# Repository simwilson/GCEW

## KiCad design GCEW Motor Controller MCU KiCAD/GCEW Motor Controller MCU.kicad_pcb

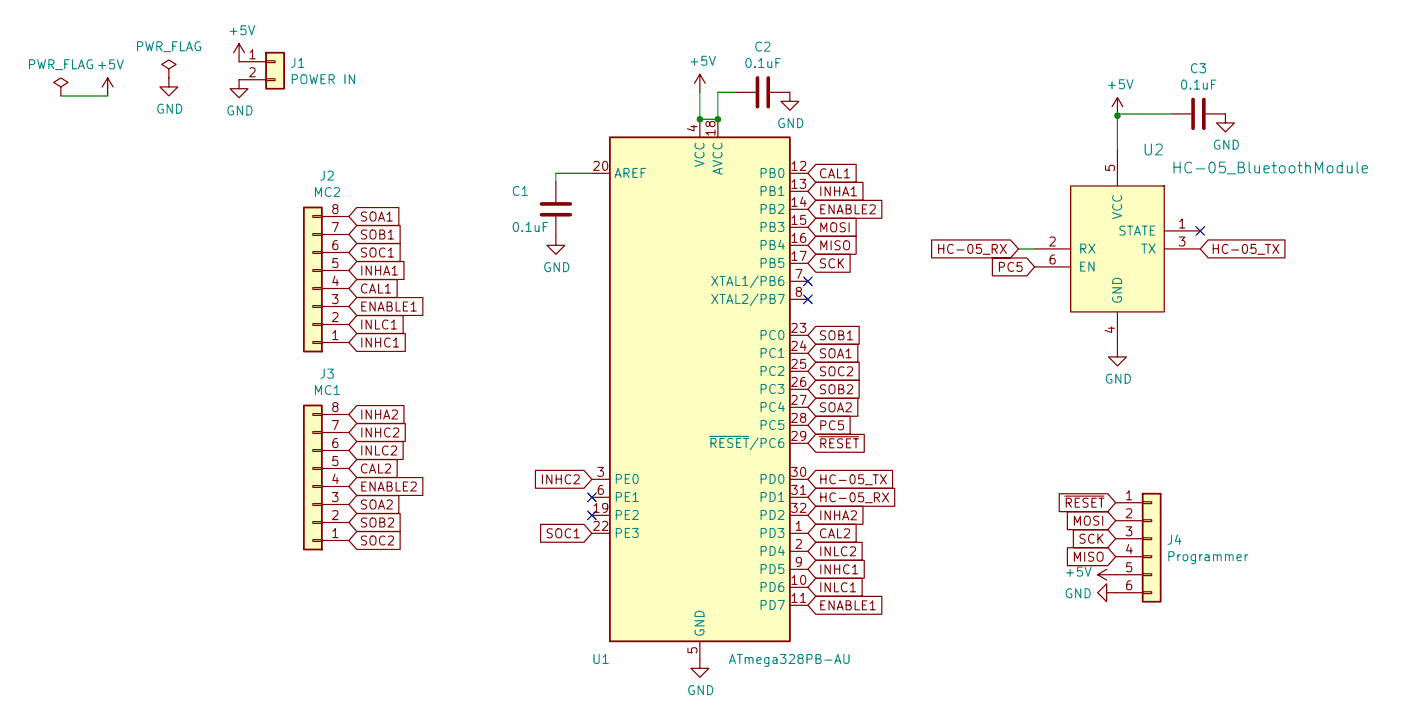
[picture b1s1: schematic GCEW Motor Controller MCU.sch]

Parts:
C1, C2, C3: 0.1uF; C_1206
J1: POWER IN; PhoenixContact_1984963_2-Pin-Connector_8A_P3.5mm
J2: MC2; PhoenixContact_1985027_8-Pin-Connector_8A_P3.5mm
J3: MC1; PhoenixContact_1985027_8-Pin-Connector_8A_P3.5mm
J4: Programmer; Pin_Header_Straight_2x03_Pitch2.54mm
U1: ATmega328PB-AU; TQFP-32_7x7mm_Pitch0.8mm
U2: HC-05_BluetoothModule; Pin_Header_Straight_1x06_Pitch2.54mm

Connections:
+5V: C2.2, C3.1, J1.1, J4.5, U1.4 (VCC), U1.18 (AVCC), U2.5 (VCC)
CAL1: J2.4, U1.12 (PB0)
CAL2: J3.5, U1.1 (PD3)
ENABLE1: J2.3, U1.11 (PD7)
ENABLE2: J3.4, U1.14 (PB2)
GND: C1.2, C2.1, C3.2, J1.2, J4.6, U1.5 (GND), U1.21 (GND), U2.4 (GND)
HC-05_RX: U1.31 (PD1), U2.2 (RX)
HC-05_TX: U1.30 (PD0), U2.3 (TX)
INHA1: J2.5, U1.13 (PB1)
INHA2: J3.8, U1.32 (PD2)
INHC1: J2.1, U1.9 (PD5)
INHC2: J3.7, U1.3 (PE0)
INLC1: J2.2, U1.10 (PD6)
INLC2: J3.6, U1.2 (PD4)
MISO: J4.4, U1.16 (PB4)
MOSI: J4.2, U1.15 (PB3)
unnamed: C1.1, U1.20 (AREF)
PC5: U1.28 (PC5), U2.6 (EN)
SCK: J4.3, U1.17 (PB5)
SOA1: J2.8, U1.24 (PC1)
SOA2: J3.3, U1.27 (PC4)
SOB1: J2.7, U1.23 (PC0)
SOB2: J3.2, U1.26 (PC3)
SOC1: J2.6, U1.22 (PE3)
SOC2: J3.1, U1.25 (PC2)
~RESET: J4.1, U1.29 (~RESET~/PC6)

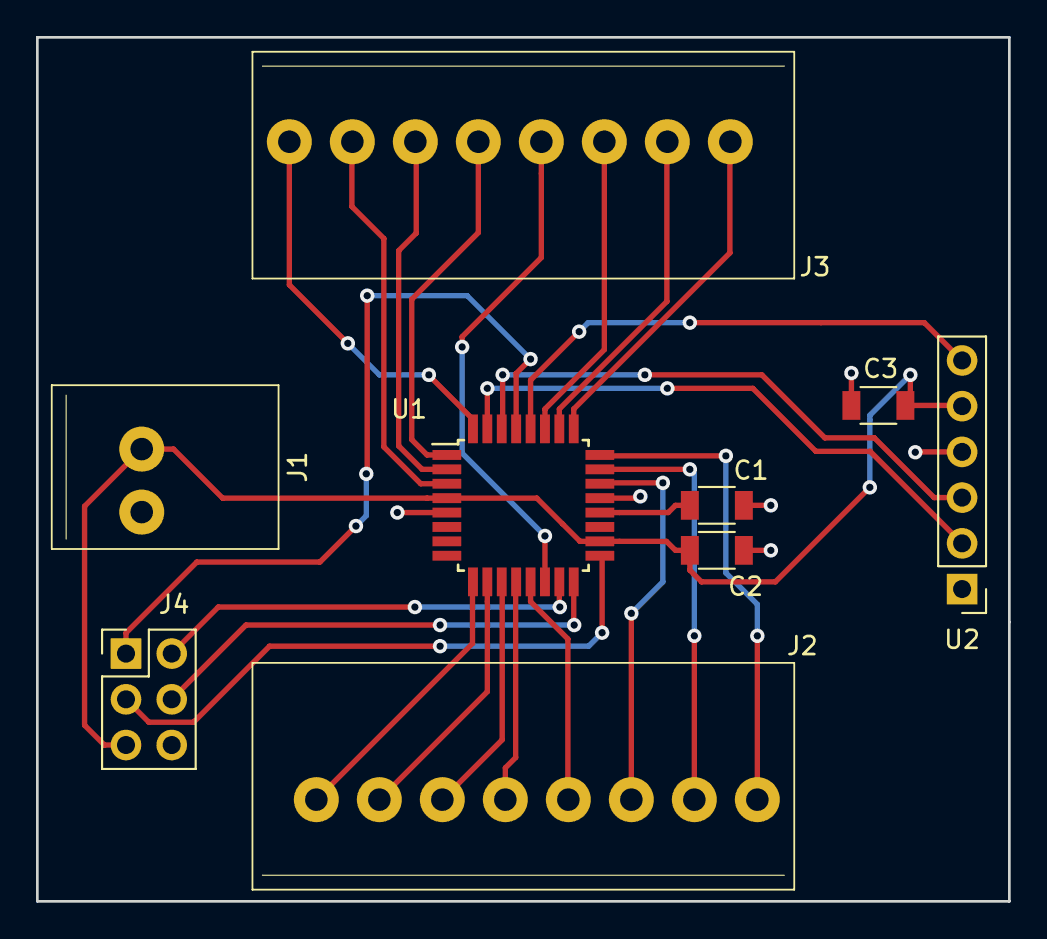
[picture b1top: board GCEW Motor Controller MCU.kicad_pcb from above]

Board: 2 copper layers, 54.0 x 48.0 mm, 9 parts (0 on the bottom side), 26 nets.

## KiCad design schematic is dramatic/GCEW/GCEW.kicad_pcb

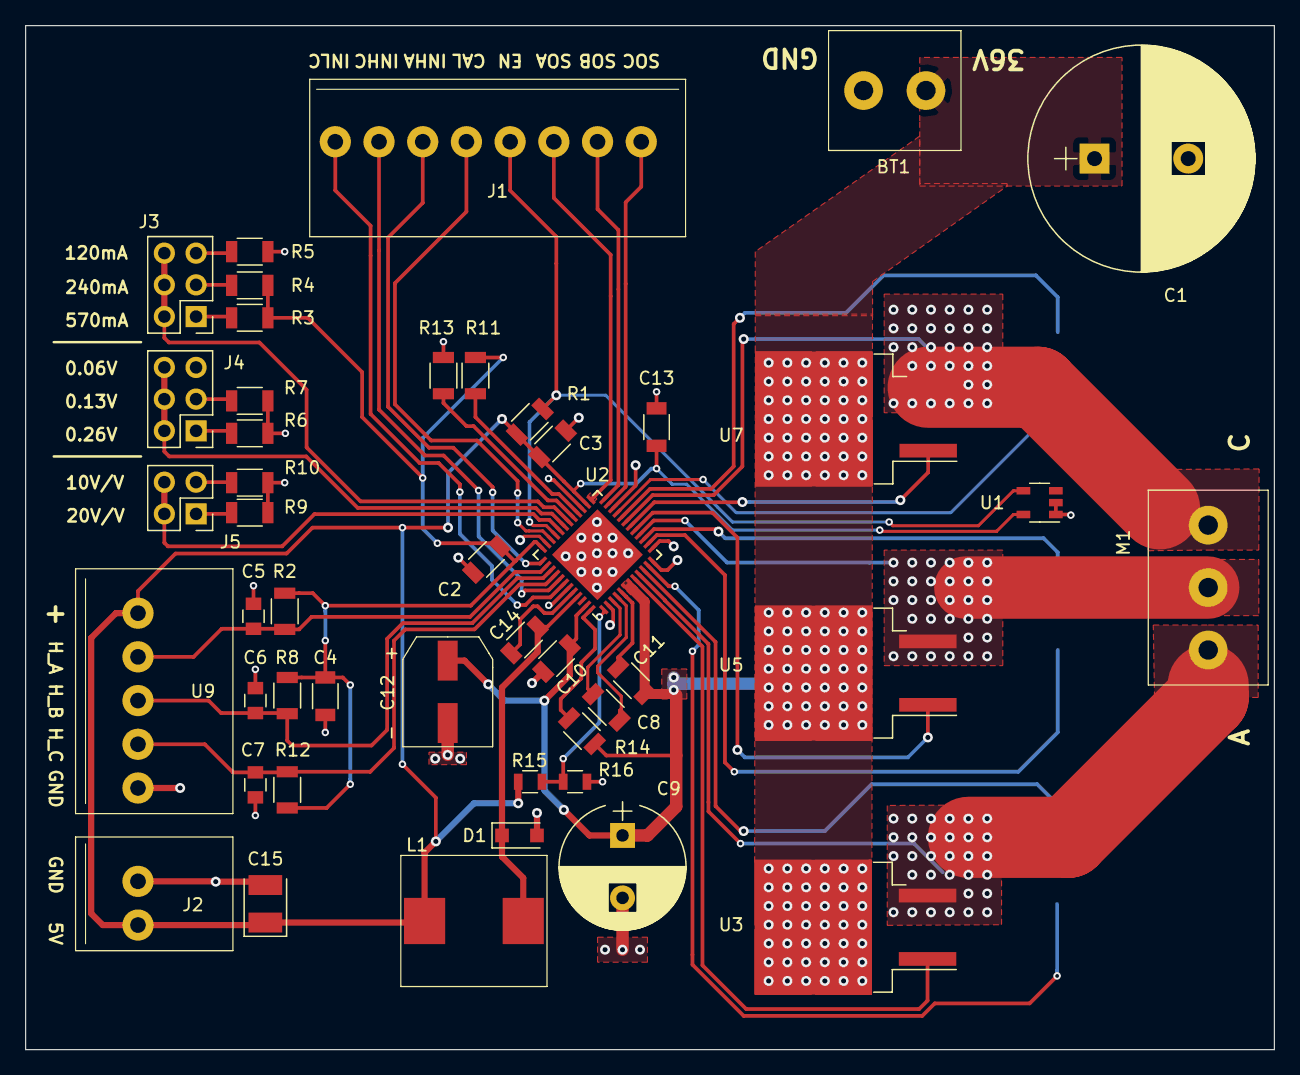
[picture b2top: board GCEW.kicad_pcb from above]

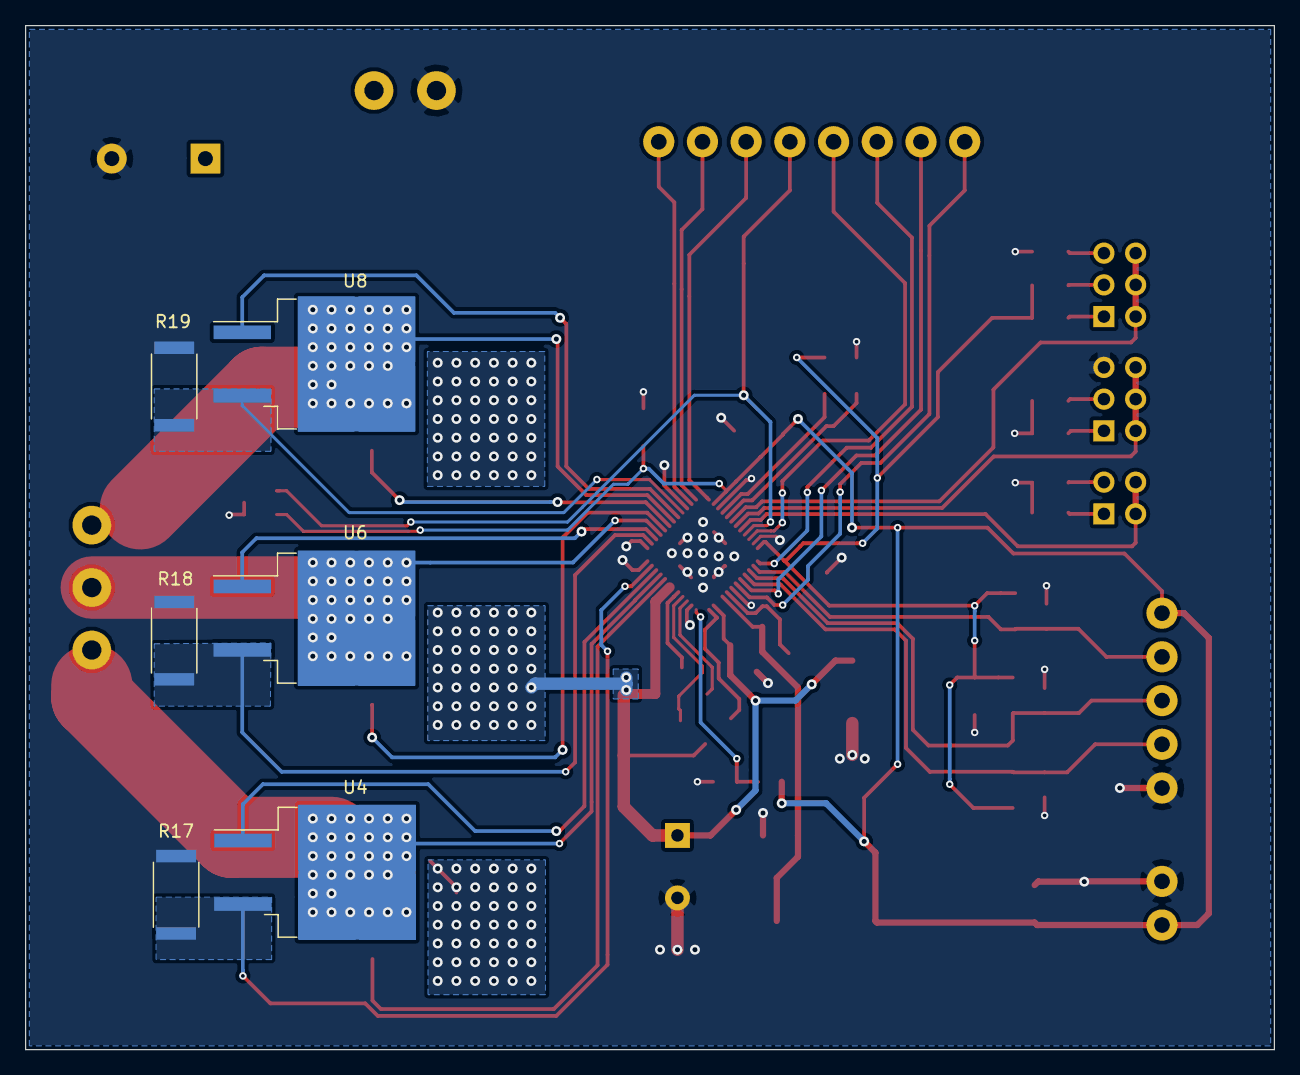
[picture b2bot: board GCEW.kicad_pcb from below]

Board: 2 copper layers, 100.0 x 82.0 mm, 52 parts (6 on the bottom side), 46 nets.

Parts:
BT1: Battery; PhoenixContact_1935776_2-Pin-Connector_32A_P5mm
C1: 2200uF; CP_Radial_D18.0mm_P7.50mm
C2, C11: 1uF 50V; C_1206
C3, C4, C13, C14: 0.1uF 25V; C_1206
C5, C6, C7: 10nF; C_0805
C8: 47nF 250V; C_1206
C9: 33uF 100V; CP_Radial_D10.0mm_P5.00mm
C10: 0.1uF 100V; C_1206
C12: 4.7uF 80V; CP_Elec_6.6x6.6mm
C15: 15uF 25V; CP_Tantalum_Case-3528
D1: 570mV, 1A; D_SOD-123F
J1: Conn_01x08; PhoenixContact_1985027_8-Pin-Connector_8A_P3.5mm
J2: Conn_01x02; PhoenixContact_1984963_2-Pin-Connector_8A_P3.5mm
J3, J4: Conn_02x03_Odd_Even; Pin_Header_Straight_2x03_Pitch2.54mm
J5: Conn_02x02_Odd_Even; Pin_Header_Straight_2x02_Pitch2.54mm
L1: 220uH; CLF10060NIT-221M-D
M1: BLDC_Motor; PhoenixContact_1991309_3-Pin-Connector_32A_P5mm
R1, R2, R8, R11, R12: 10K; R_1206
R3, R7: 18K; R_1206
R4, R6: 75K; R_1206
R5, R9, R13: 1M; R_1206
R10: 47K; R_1206
R14: 100K; R_1206
R15: 57.6K; R_0805
R16: 10.4K; R_0805
R17, R18, R19: 2milli; R_2512
U1: LM26CIM5-VHA; SOT-23-5
U2: DRV8323RH; TI-RGZ-QFN-48-1EP_7x7mm_Pitch0.5mm
U3, U4, U5, U6, U7, U8: IPB029N06N; TO-263-2
U9: BLDC_Hall_Sensor; PhoenixContact_1984992_5-Pin-Connector_8A_P3.5mm

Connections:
36V: BT1.1, C1.1, C9.1, C10.1, C11.2, C12.1, R14.2, U2.6, U2.7, U2.47, U3.2, U5.2, U7.2
CAL: J1.5, U2.34
DVDD: C2.1, C4.1, R2.1, R3.2, R4.2, R8.1, R11.1, R12.1, U2.36
ENABLE: J1.4, R1.2, U1.5, U2.33
GAIN: J5.2, J5.4, U2.32
GHA: U2.8, U3.1
GHB: U2.17, U5.1
GHC: U2.18, U7.1
GLA: U2.10, U4.1
GLB: U2.15, U6.1
GLC: U2.20, U8.1
Hall_A: C5.1, R2.2, U2.38, U9.2
Hall_B: C6.1, R8.2, U2.39, U9.3
Hall_C: C7.1, R12.2, U2.40, U9.4
IDRIVE: J3.2, J3.4, J3.6, U2.30
INHA: J1.6, U2.37
INHC: J1.7, U2.41
INLC: J1.8, U2.42
unnamed: C8.1, U2.3
unnamed: C8.2, U2.4
unnamed: C11.1, U2.5
unnamed: C14.1, U2.44
unnamed: C14.2, D1.1, L1.1, U2.45
unnamed: J3.1, R3.1
unnamed: J3.3, R4.1
unnamed: J3.5, R5.1
unnamed: J4.1, R6.1
unnamed: J4.3, R7.1
unnamed: J5.1, R9.1
unnamed: J5.3, R10.1
unnamed: M1.1, U2.9, U3.3, U4.2
unnamed: M1.2, U2.16, U5.3, U6.2
unnamed: M1.3, U2.19, U7.3, U8.2
unnamed: R11.2, U2.28
unnamed: R13.1, U2.29
unnamed: R14.1, U2.48
unnamed: R15.2, R16.1, U2.1
SNA: BT1.2, C1.2, C2.2, C3.1, C4.2, C5.2, C6.2, C7.2, C9.2, C10.2, C12.2, C13.2, C15.2, D1.2, J2.1, J4.5, R5.2, R6.2, R7.2, R9.2, R10.2, R13.2, R16.2, R17.2, R18.2, R19.2, U1.1, U1.2, U2.2, U2.12, U2.13, U2.22, U2.27, U2.35, U2.43, U2.49, U9.5
SOA: J1.3, U2.25
SOB: J1.2, U2.24
SOC: J1.1, U2.23
SPA: R17.1, U2.11, U4.3
SPB: R18.1, U2.14, U6.3
SPC: R19.1, U2.21, U8.3
VDS: J4.2, J4.4, J4.6, U2.31
VREF: C3.2, C13.1, C15.1, J2.2, L1.2, R1.1, R15.1, U1.4, U2.26, U9.1

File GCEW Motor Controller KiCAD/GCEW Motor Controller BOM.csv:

Id,Designator,Package,Quantity,Designation,Supplier and ref,Column1,_1
1,BT1,PhoenixContact_1935776_2-Pin-Connector_32A_P5mm,1,Battery,,,
2,C1,CP_Radial_D18.0mm_P7.50mm,1,2200uF,,,
3,"C2,C11",C_1206,2,1uF 50V,,,
4,"C3,C4,C13,C14",C_1206,4,0.1uF 25V,,,
5,"C5,C6,C7",C_0805,3,10nF,,,
6,C8,C_1206,1,47nF 250V,,,
7,C9,CP_Radial_D10.0mm_P5.00mm,1,33uF 100V,,,
8,C10,C_1206,1,0.1uF 100V,,,
9,C12,CP_Elec_6.6x6.6mm,1,4.7uF 80V,,,
10,C15,CP_Tantalum_Case-3528,1,15uF 25V,,,
11,D1,D_SOD-123F,1,"570mV, 1A",,,
12,J1,PhoenixContact_1985027_8-Pin-Connector_8A_P3.5mm,1,Conn_01x08,,,
13,J2,PhoenixContact_1984963_2-Pin-Connector_8A_P3.5mm,1,Conn_01x02,,,
14,"J3,J4",Pin_Header_Straight_2x03_Pitch2.54mm,2,Conn_02x03_Odd_Even,,,
15,J5,Pin_Header_Straight_2x02_Pitch2.54mm,1,Conn_02x02_Odd_Even,,,
16,L1,CLF10060NIT-221M-D,1,220uH,,,
17,M1,PhoenixContact_1991309_3-Pin-Connector_32A_P5mm,1,BLDC_Motor,,,
18,"R1,R2,R8,R11,R12",R_1206,5,10K,,,
19,"R3,R7",R_1206,2,18K,,,
20,"R4,R6",R_1206,2,75K,,,
21,"R5,R9,R13",R_1206,3,1M,,,
22,R10,R_1206,1,47K,,,
23,R14,R_1206,1,100K,,,
24,R15,R_0805,1,57.6K,,,
25,R16,R_0805,1,10.4K,,,
26,"R17,R18,R19",R_2512,3,2milli,,,
27,U1,SOT-23-5,1,LM26CIM5-VHA,,,
28,U2,TI-RGZ-QFN-48-1EP_7x7mm_Pitch0.5mm,1,DRV8323RH,,,
29,"U3,U4,U5,U6,U7,U8",TO-263-2,6,IPB029N06N,,,
30,U9,PhoenixContact_1984992_5-Pin-Connector_8A_P3.5mm,1,BLDC_Hall_Sensor,,,

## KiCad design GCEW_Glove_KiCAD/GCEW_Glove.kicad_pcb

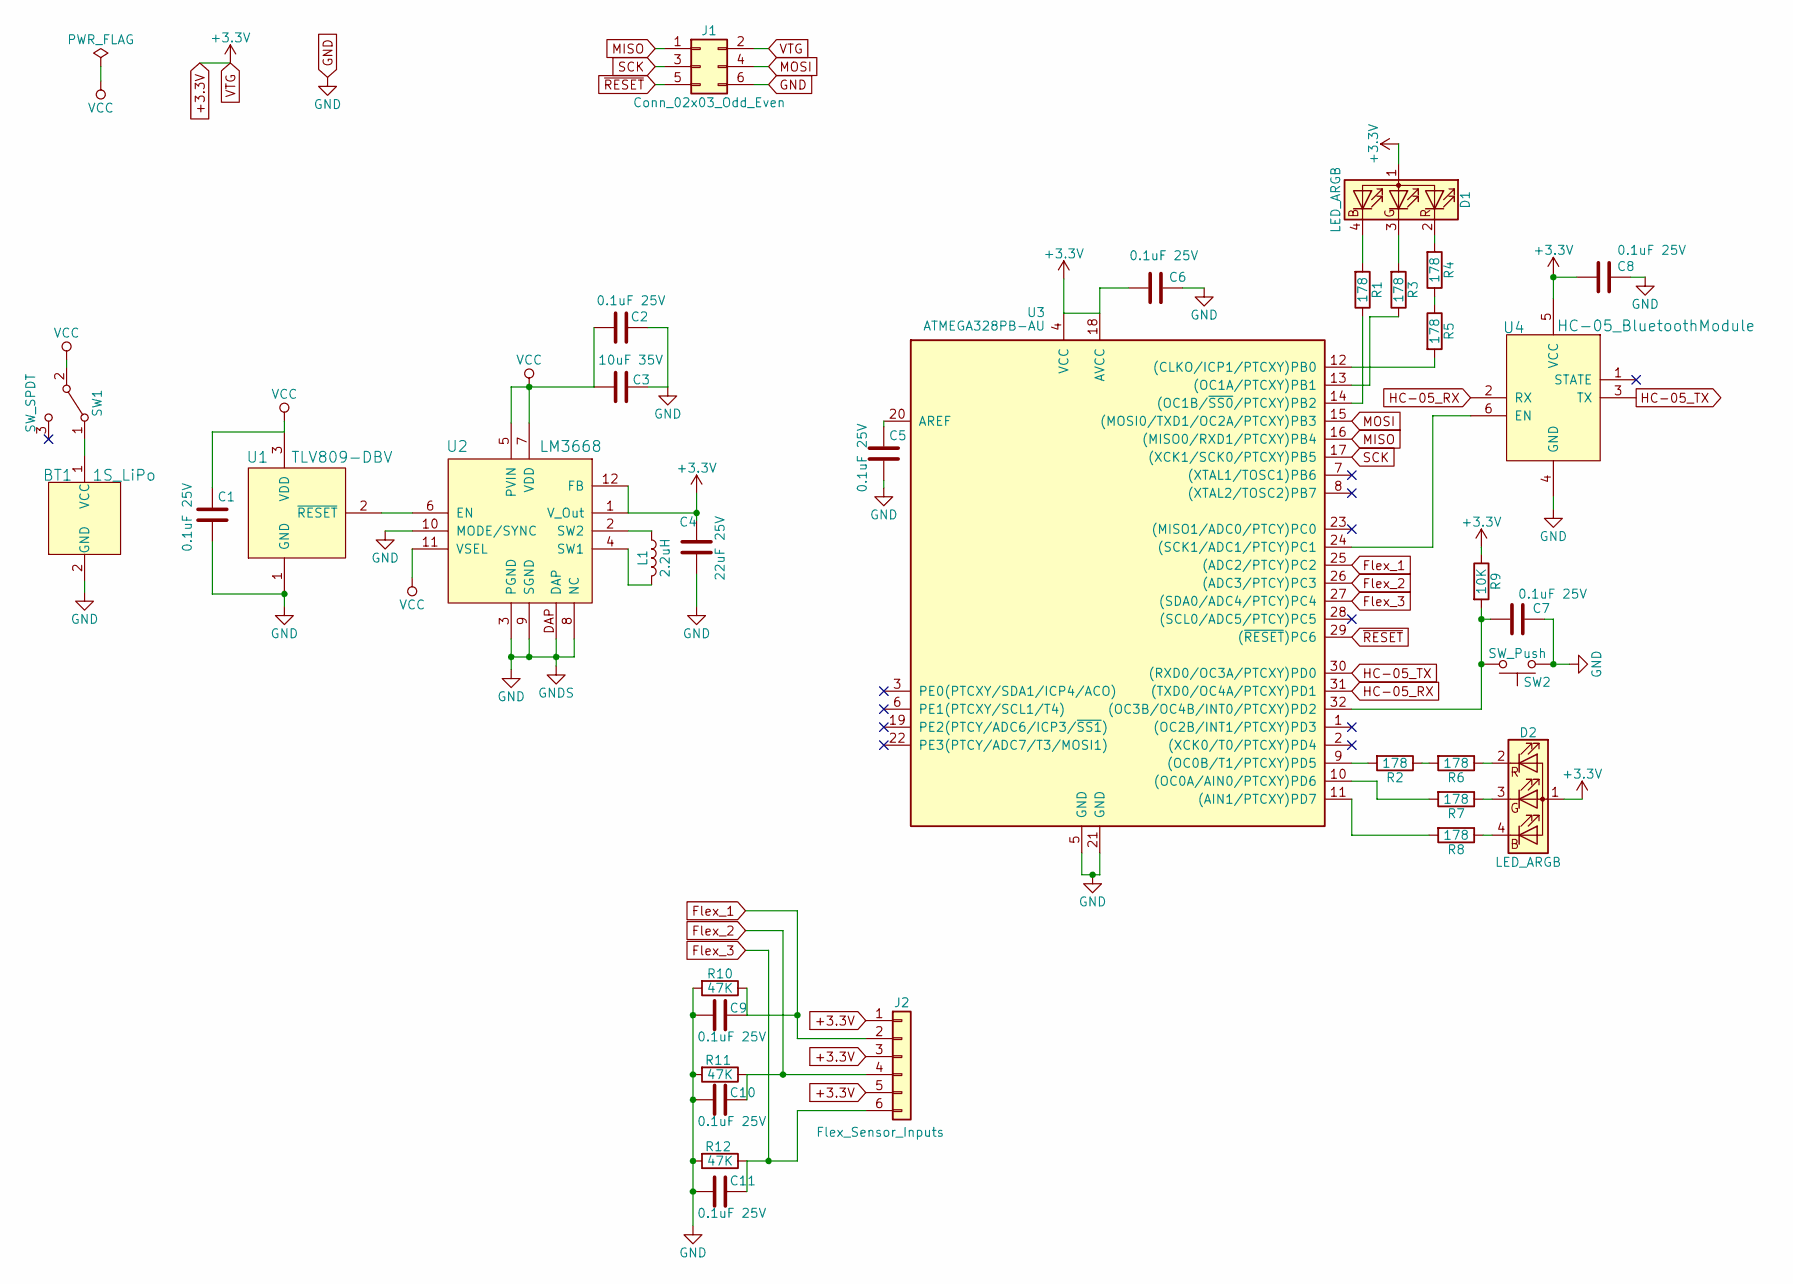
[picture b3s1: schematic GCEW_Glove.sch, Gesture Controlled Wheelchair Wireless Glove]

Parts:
BT1: 1S_LiPo; 1S_150mAH_LiPo
C1, C2, C5, C6, C7, C8, C9, C10, C11: 0.1uF 25V; C_1206
C3: 10uF 35V; C_1206
C4: 22uF 25V; C_0805
D1, D2: LED_ARGB; SML-LX0404SIUPGUSB_RGB_LED
J1: Conn_02x03_Odd_Even; Pin_Header_Straight_2x03_Pitch2.54mm
J2: Flex_Sensor_Inputs; Pin_Header_Straight_1x06_Pitch2.54mm
L1: 2.2uH; L_Taiyo-Yuden_NR-40xx
R1, R2, R3, R4, R5, R6, R7, R8: 178; R_1206
R9: 10K; R_1206
R10, R11, R12: 47K; R_1206
SW1: SW_SPDT; SPDT_TH_4.2x11.8mm
SW2: SW_Push; MOM_PushButton_2Pins_3.5x6mm
U1: TLV809-DBV; SOT-23-3
U2: LM3668; WSON-12-1EP_3x3mm_Pitch0.4mm
U3: ATMEGA328PB-AU; TQFP-32_7x7mm_Pitch0.8mm
U4: HC-05_BluetoothModule; Pin_Header_Straight_1x06_Pitch2.54mm

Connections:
+3.3V: C4.1, C6.2, C8.2, D1.1 (A), D2.1 (A), J1.2, J2.1, J2.3, J2.5, R9.1, U2.1 (V_Out), U2.12 (FB), U3.4 (VCC), U3.18 (AVCC), U4.5 (VCC)
Flex_1: C9.1, J2.2, R10.1, U3.25 ((ADC2/PTCY)PC2)
Flex_2: C10.1, J2.4, R11.1, U3.26 ((ADC3/PTCY)PC3)
Flex_3: C11.1, J2.6, R12.1, U3.27 ((SDA0/ADC4/PTCY)PC4)
GND: BT1.2 (GND), C1.2, C2.1, C3.1, C4.2, C5.2, C6.1, C7.1, C8.1, C9.2, C10.2, C11.2, J1.6, R10.2, R11.2, R12.2, SW2.1, U1.1 (GND), U2.3 (PGND), U2.8 (NC), U2.9 (SGND), U2.10 (MODE/SYNC), U2.DAP, U3.5 (GND), U3.21 (GND), U4.4 (GND)
HC-05_RX: U3.31 ((TXD0/OC4A/PTCXY)PD1), U4.2 (RX)
HC-05_TX: U3.30 ((RXD0/OC3A/PTCXY)PD0), U4.3 (TX)
MISO: J1.1, U3.16 ((MISO0/RXD1/PTCXY)PB4)
MOSI: J1.4, U3.15 ((MOSI0/TXD1/OC2A/PTCXY)PB3)
unnamed: BT1.1 (VCC), SW1.1 (A)
unnamed: C5.1, U3.20 (AREF)
unnamed: C7.2, R9.2, SW2.2, U3.32 ((OC3B/OC4B/INT0/PTCXY)PD2)
unnamed: D1.2 (RK), R4.2
unnamed: D1.3 (GK), R3.2
unnamed: D1.4 (BK), R1.2
unnamed: D2.2 (RK), R6.1
unnamed: D2.3 (GK), R7.1
unnamed: D2.4 (BK), R8.1
unnamed: L1.1, U2.2 (SW2)
unnamed: L1.2, U2.4 (SW1)
unnamed: R1.1, U3.14 ((OC1B/~SS0~/PTCXY)PB2)
unnamed: R2.1, R6.2
unnamed: R2.2, U3.9 ((OC0B/T1/PTCXY)PD5)
unnamed: R3.1, U3.13 ((OC1A/PTCXY)PB1)
unnamed: R4.1, R5.1
unnamed: R5.2, U3.12 ((CLKO/ICP1/PTCXY)PB0)
unnamed: R7.2, U3.10 ((OC0A/AIN0/PTCXY)PD6)
unnamed: R8.2, U3.11 ((AIN1/PTCXY)PD7)
unnamed: U1.2 (~RESET), U2.6 (EN)
unnamed: U3.24 ((SCK1/ADC1/PTCY)PC1), U4.6 (EN)
SCK: J1.3, U3.17 ((XCK1/SCK0/PTCXY)PB5)
VCC: C1.1, C2.2, C3.2, SW1.2 (B), U1.3 (VDD), U2.5 (PVIN), U2.7 (VDD), U2.11 (VSEL)
~RESET: J1.5, U3.29 ((~RESET~)PC6)

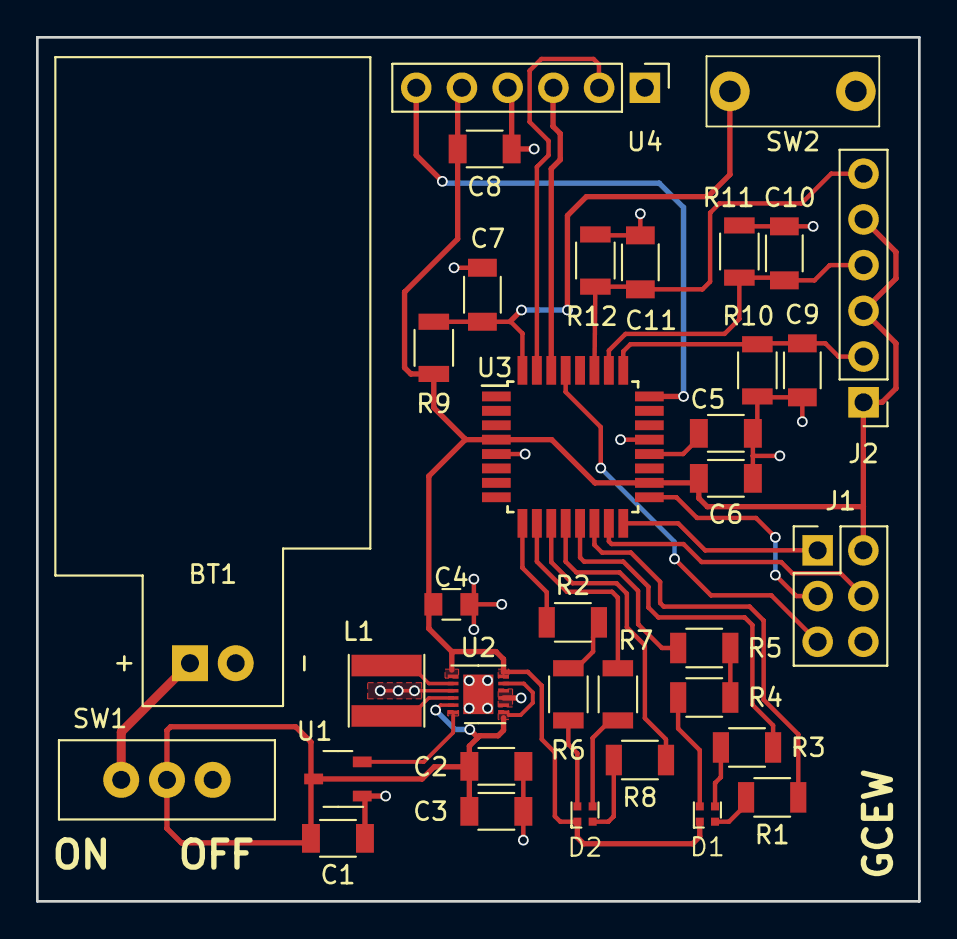
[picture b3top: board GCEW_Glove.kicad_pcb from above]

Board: 2 copper layers, 49.0 x 48.0 mm, 35 parts (0 on the bottom side), 33 nets.

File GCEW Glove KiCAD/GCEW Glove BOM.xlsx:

Id | Designator | Package | Quantity | Designation | Supplier and ref | Column1 | _1
1 | U2 | WSON-12-1EP_3x3mm_Pitch0.4mm | 1 | LM3668
2 | BT1 | 1S_150mAH_LiPo | 1 | 1S_LiPo
3 | C1,C2,C5,C6,C7,C8,C9,C10,C11 | C_1206 | 9 | 0.1uF 25V
4 | C3 | C_1206 | 1 | 10uF 35V
5 | J1 | Pin_Header_Straight_2x03_Pitch2.54mm | 1 | Conn_02x03_Odd_Even
6 | J2 | Pin_Header_Straight_1x06_Pitch2.54mm | 1 | Flex_Sensor_Inputs
7 | L1 | L_Taiyo-Yuden_NR-40xx | 1 | 2.2uH
8 | R1,R2,R3,R4,R5,R6,R7,R8 | R_1206 | 8 | 178
9 | R9 | R_1206 | 1 | 10K
10 | R10,R11,R12 | R_1206 | 3 | 47K
11 | SW1 | SPDT_TH_4.2x11.8mm | 1 | SW_SPDT
12 | SW2 | MOM_PushButton_2Pins_3.5x6mm | 1 | SW_Push
13 | U3 | TQFP-32_7x7mm_Pitch0.8mm | 1 | ATMEGA328PB-AU
14 | U4 | Pin_Header_Straight_1x06_Pitch2.54mm | 1 | HC-05_BluetoothModule
15 | D1,D2 | SML-LX0404SIUPGUSB_RGB_LED | 2 | LED_ARGB
16 | U1 | SOT-23-3 | 1 | TLV809-DBV
17 | C4 | C_0805 | 1 | 22uF 25V

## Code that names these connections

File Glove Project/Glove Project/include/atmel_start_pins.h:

/*
 * Code generated from Atmel Start.
 *
 * This file will be overwritten when reconfiguring your Atmel Start project.
 * Please copy examples or other code you want to keep to a separate file
 * to avoid losing it when reconfiguring.
 */
#ifndef ATMEL_START_PINS_H_INCLUDED
#define ATMEL_START_PINS_H_INCLUDED

#include <port.h>

/**
 * \brief Set PC2 pull mode
 *
 * Configure pin to pull up, down or disable pull mode, supported pull
 * modes are defined by device used
 *
 * \param[in] pull_mode Pin pull mode
 */
static inline void PC2_set_pull_mode(const enum port_pull_mode pull_mode)
{
	PORTC_set_pin_pull_mode(2, pull_mode);
}

/**
 * \brief Set PC2 data direction
 *
 * Select if the pin data direction is input, output or disabled.
 * If disabled state is not possible, this function throws an assert.
 *
 * \param[in] direction PORT_DIR_IN  = Data direction in
 *                      PORT_DIR_OUT = Data direction out
 *                      PORT_DIR_OFF = Disables the pin
 *                      (low power state)
 */
static inline void PC2_set_dir(const enum port_dir dir)
{
	PORTC_set_pin_dir(2, dir);
}

/**
 * \brief Set PC2 level
 *
 * Sets output level on a pin
 *
 * \param[in] level true  = Pin level set to "high" state
 *                  false = Pin level set to "low" state
 */
static inline void PC2_set_level(const bool level)
{
	PORTC_set_pin_level(2, level);
}

/**
 * \brief Toggle output level on PC2
 *
 * Toggle the pin level
 */
static inline void PC2_toggle_level()
{
	PORTC_toggle_pin_level(2);
}

/**
 * \brief Get level on PC2
 *
 * Reads the level on a pin
 */
static inline bool PC2_get_level()
{
	return PORTC_get_pin_level(2);
}

/**
 * \brief Set PC3 pull mode
 *
 * Configure pin to pull up, down or disable pull mode, supported pull
 * modes are defined by device used
 *
 * \param[in] pull_mode Pin pull mode
 */
static inline void PC3_set_pull_mode(const enum port_pull_mode pull_mode)
{
	PORTC_set_pin_pull_mode(3, pull_mode);
}

/**
 * \brief Set PC3 data direction
 *
 * Select if the pin data direction is input, output or disabled.
 * If disabled state is not possible, this function throws an assert.
 *
 * \param[in] direction PORT_DIR_IN  = Data direction in
 *                      PORT_DIR_OUT = Data direction out
 *                      PORT_DIR_OFF = Disables the pin
 *                      (low power state)
 */
static inline void PC3_set_dir(const enum port_dir dir)
{
	PORTC_set_pin_dir(3, dir);
}

/**
 * \brief Set PC3 level
 *
 * Sets output level on a pin
 *
 * \param[in] level true  = Pin level set to "high" state
 *                  false = Pin level set to "low" state
 */
static inline void PC3_set_level(const bool level)
{
	PORTC_set_pin_level(3, level);
}

/**
 * \brief Toggle output level on PC3
 *
 * Toggle the pin level
 */
static inline void PC3_toggle_level()
{
	PORTC_toggle_pin_level(3);
}

/**
 * \brief Get level on PC3
 *
 * Reads the level on a pin
 */
static inline bool PC3_get_level()
{
	return PORTC_get_pin_level(3);
}

/**
 * \brief Set PC4 pull mode
 *
 * Configure pin to pull up, down or disable pull mode, supported pull
 * modes are defined by device used
 *
 * \param[in] pull_mode Pin pull mode
 */
static inline void PC4_set_pull_mode(const enum port_pull_mode pull_mode)
{
	PORTC_set_pin_pull_mode(4, pull_mode);
}

/**
 * \brief Set PC4 data direction
 *
 * Select if the pin data direction is input, output or disabled.
 * If disabled state is not possible, this function throws an assert.
 *
 * \param[in] direction PORT_DIR_IN  = Data direction in
 *                      PORT_DIR_OUT = Data direction out
 *                      PORT_DIR_OFF = Disables the pin
 *                      (low power state)
 */
static inline void PC4_set_dir(const enum port_dir dir)
{
	PORTC_set_pin_dir(4, dir);
}

/**
 * \brief Set PC4 level
 *
 * Sets output level on a pin
 *
 * \param[in] level true  = Pin level set to "high" state
 *                  false = Pin level set to "low" state
 */
static inline void PC4_set_level(const bool level)
{
	PORTC_set_pin_level(4, level);
}

/**
 * \brief Toggle output level on PC4
 *
 * Toggle the pin level
 */
static inline void PC4_toggle_level()
{
	PORTC_toggle_pin_level(4);
}

/**
 * \brief Get level on PC4
 *
 * Reads the level on a pin
 */
static inline bool PC4_get_level()
{
	return PORTC_get_pin_level(4);
}

/**
 * \brief Set PD0 pull mode
 *
 * Configure pin to pull up, down or disable pull mode, supported pull
 * modes are defined by device used
 *
 * \param[in] pull_mode Pin pull mode
 */
static inline void PD0_set_pull_mode(const enum port_pull_mode pull_mode)
{
	PORTD_set_pin_pull_mode(0, pull_mode);
}

/**
 * \brief Set PD0 data direction
 *
 * Select if the pin data direction is input, output or disabled.
 * If disabled state is not possible, this function throws an assert.
 *
 * \param[in] direction PORT_DIR_IN  = Data direction in
 *                      PORT_DIR_OUT = Data direction out
 *                      PORT_DIR_OFF = Disables the pin
 *                      (low power state)
 */
static inline void PD0_set_dir(const enum port_dir dir)
{
	PORTD_set_pin_dir(0, dir);
}

/**
 * \brief Set PD0 level
 *
 * Sets output level on a pin
 *
 * \param[in] level true  = Pin level set to "high" state
 *                  false = Pin level set to "low" state
 */
static inline void PD0_set_level(const bool level)
{
	PORTD_set_pin_level(0, level);
}

/**
 * \brief Toggle output level on PD0
 *
 * Toggle the pin level
 */
static inline void PD0_toggle_level()
{
	PORTD_toggle_pin_level(0);
}

/**
 * \brief Get level on PD0
 *
 * Reads the level on a pin
 */
static inline bool PD0_get_level()
{
	return PORTD_get_pin_level(0);
}

/**
 * \brief Set PD1 pull mode
 *
 * Configure pin to pull up, down or disable pull mode, supported pull
 * modes are defined by device used
 *
 * \param[in] pull_mode Pin pull mode
 */
static inline void PD1_set_pull_mode(const enum port_pull_mode pull_mode)
{
	PORTD_set_pin_pull_mode(1, pull_mode);
}

/**
 * \brief Set PD1 data direction
 *
 * Select if the pin data direction is input, output or disabled.
 * If disabled state is not possible, this function throws an assert.
 *
 * \param[in] direction PORT_DIR_IN  = Data direction in
 *                      PORT_DIR_OUT = Data direction out
 *                      PORT_DIR_OFF = Disables the pin
 *                      (low power state)
 */
static inline void PD1_set_dir(const enum port_dir dir)
{
	PORTD_set_pin_dir(1, dir);
}

/**
 * \brief Set PD1 level
 *
 * Sets output level on a pin
 *
 * \param[in] level true  = Pin level set to "high" state
 *                  false = Pin level set to "low" state
 */
static inline void PD1_set_level(const bool level)
{
	PORTD_set_pin_level(1, level);
}

/**
 * \brief Toggle output level on PD1
 *
 * Toggle the pin level
 */
static inline void PD1_toggle_level()
{
	PORTD_toggle_pin_level(1);
}

/**
 * \brief Get level on PD1
 *
 * Reads the level on a pin
 */
static inline bool PD1_get_level()
{
	return PORTD_get_pin_level(1);
}

#endif /* ATMEL_START_PINS_H_INCLUDED */

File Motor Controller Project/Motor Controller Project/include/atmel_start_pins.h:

/*
 * Code generated from Atmel Start.
 *
 * This file will be overwritten when reconfiguring your Atmel Start project.
 * Please copy examples or other code you want to keep to a separate file
 * to avoid losing it when reconfiguring.
 */
#ifndef ATMEL_START_PINS_H_INCLUDED
#define ATMEL_START_PINS_H_INCLUDED

#include <port.h>

/**
 * \brief Set PB1 pull mode
 *
 * Configure pin to pull up, down or disable pull mode, supported pull
 * modes are defined by device used
 *
 * \param[in] pull_mode Pin pull mode
 */
static inline void PB1_set_pull_mode(const enum port_pull_mode pull_mode)
{
	PORTB_set_pin_pull_mode(1, pull_mode);
}

/**
 * \brief Set PB1 data direction
 *
 * Select if the pin data direction is input, output or disabled.
 * If disabled state is not possible, this function throws an assert.
 *
 * \param[in] direction PORT_DIR_IN  = Data direction in
 *                      PORT_DIR_OUT = Data direction out
 *                      PORT_DIR_OFF = Disables the pin
 *                      (low power state)
 */
static inline void PB1_set_dir(const enum port_dir dir)
{
	PORTB_set_pin_dir(1, dir);
}

/**
 * \brief Set PB1 level
 *
 * Sets output level on a pin
 *
 * \param[in] level true  = Pin level set to "high" state
 *                  false = Pin level set to "low" state
 */
static inline void PB1_set_level(const bool level)
{
	PORTB_set_pin_level(1, level);
}

/**
 * \brief Toggle output level on PB1
 *
 * Toggle the pin level
 */
static inline void PB1_toggle_level()
{
	PORTB_toggle_pin_level(1);
}

/**
 * \brief Get level on PB1
 *
 * Reads the level on a pin
 */
static inline bool PB1_get_level()
{
	return PORTB_get_pin_level(1);
}

/**
 * \brief Set PD0 pull mode
 *
 * Configure pin to pull up, down or disable pull mode, supported pull
 * modes are defined by device used
 *
 * \param[in] pull_mode Pin pull mode
 */
static inline void PD0_set_pull_mode(const enum port_pull_mode pull_mode)
{
	PORTD_set_pin_pull_mode(0, pull_mode);
}

/**
 * \brief Set PD0 data direction
 *
 * Select if the pin data direction is input, output or disabled.
 * If disabled state is not possible, this function throws an assert.
 *
 * \param[in] direction PORT_DIR_IN  = Data direction in
 *                      PORT_DIR_OUT = Data direction out
 *                      PORT_DIR_OFF = Disables the pin
 *                      (low power state)
 */
static inline void PD0_set_dir(const enum port_dir dir)
{
	PORTD_set_pin_dir(0, dir);
}

/**
 * \brief Set PD0 level
 *
 * Sets output level on a pin
 *
 * \param[in] level true  = Pin level set to "high" state
 *                  false = Pin level set to "low" state
 */
static inline void PD0_set_level(const bool level)
{
	PORTD_set_pin_level(0, level);
}

/**
 * \brief Toggle output level on PD0
 *
 * Toggle the pin level
 */
static inline void PD0_toggle_level()
{
	PORTD_toggle_pin_level(0);
}

/**
 * \brief Get level on PD0
 *
 * Reads the level on a pin
 */
static inline bool PD0_get_level()
{
	return PORTD_get_pin_level(0);
}

/**
 * \brief Set PD1 pull mode
 *
 * Configure pin to pull up, down or disable pull mode, supported pull
 * modes are defined by device used
 *
 * \param[in] pull_mode Pin pull mode
 */
static inline void PD1_set_pull_mode(const enum port_pull_mode pull_mode)
{
	PORTD_set_pin_pull_mode(1, pull_mode);
}

/**
 * \brief Set PD1 data direction
 *
 * Select if the pin data direction is input, output or disabled.
 * If disabled state is not possible, this function throws an assert.
 *
 * \param[in] direction PORT_DIR_IN  = Data direction in
 *                      PORT_DIR_OUT = Data direction out
 *                      PORT_DIR_OFF = Disables the pin
 *                      (low power state)
 */
static inline void PD1_set_dir(const enum port_dir dir)
{
	PORTD_set_pin_dir(1, dir);
}

/**
 * \brief Set PD1 level
 *
 * Sets output level on a pin
 *
 * \param[in] level true  = Pin level set to "high" state
 *                  false = Pin level set to "low" state
 */
static inline void PD1_set_level(const bool level)
{
	PORTD_set_pin_level(1, level);
}

/**
 * \brief Toggle output level on PD1
 *
 * Toggle the pin level
 */
static inline void PD1_toggle_level()
{
	PORTD_toggle_pin_level(1);
}

/**
 * \brief Get level on PD1
 *
 * Reads the level on a pin
 */
static inline bool PD1_get_level()
{
	return PORTD_get_pin_level(1);
}

/**
 * \brief Set PD2 pull mode
 *
 * Configure pin to pull up, down or disable pull mode, supported pull
 * modes are defined by device used
 *
 * \param[in] pull_mode Pin pull mode
 */
static inline void PD2_set_pull_mode(const enum port_pull_mode pull_mode)
{
	PORTD_set_pin_pull_mode(2, pull_mode);
}

/**
 * \brief Set PD2 data direction
 *
 * Select if the pin data direction is input, output or disabled.
 * If disabled state is not possible, this function throws an assert.
 *
 * \param[in] direction PORT_DIR_IN  = Data direction in
 *                      PORT_DIR_OUT = Data direction out
 *                      PORT_DIR_OFF = Disables the pin
 *                      (low power state)
 */
static inline void PD2_set_dir(const enum port_dir dir)
{
	PORTD_set_pin_dir(2, dir);
}

/**
 * \brief Set PD2 level
 *
 * Sets output level on a pin
 *
 * \param[in] level true  = Pin level set to "high" state
 *                  false = Pin level set to "low" state
 */
static inline void PD2_set_level(const bool level)
{
	PORTD_set_pin_level(2, level);
}

/**
 * \brief Toggle output level on PD2
 *
 * Toggle the pin level
 */
static inline void PD2_toggle_level()
{
	PORTD_toggle_pin_level(2);
}

/**
 * \brief Get level on PD2
 *
 * Reads the level on a pin
 */
static inline bool PD2_get_level()
{
	return PORTD_get_pin_level(2);
}

#endif /* ATMEL_START_PINS_H_INCLUDED */

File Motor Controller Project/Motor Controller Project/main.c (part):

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#define NUMBER_OF_STEPS 30


//OUTPUT on PB2
volatile PWM_0_register_t PWM_0_duty = STOPPED;
volatile PWM_1_register_t PWM_1_duty = STOPPED;

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	uint8_t CURR_DIRECTION = FORWARD;
	uint8_t GOAL_DIRECTION = FORWARD;
	
	DDRB |= 0x07;// Set pins PB0 - PB2 as Outputs, for Timer 1 and
	DDRD |= 0x74; // Set pin PD2 as Output , for Timer 3
	DDRE |= 0x01;
	
	PORTD |= 0x50;
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				}
				else{
					CURR_DIRECTION = REVERSE;
					PORTD |= 0x20;  // LEFT MOTOR PD5
					PORTE = 0x00;
					
				}
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
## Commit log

2018-09-29 Initial KiCAD Library
    KiCAD Library Folder with custom designed components for GCEW PCB
2018-10-01 GCEW Glove KiCAD Schematic / PCB Files
2018-10-03 GCEW Glove Schematic Update 1
2018-10-06 GCEW Glove Schematic Update 2
2018-10-06 GCEW Glove Code -Atmel Studio
    Test code generated in Atmel Studio for the ATmega328PB-AN MCU on the GCEW Glove
2018-10-07 SolidWorks Motor Mount Files and Renderings
2018-10-12 GCEW Glove Code Update 1
    Added ADC Functionality using AVcc as reference voltage. Added multiple methods for writing various datatypes though UART.
2018-10-16 GCEW Glove Code Update 2
    Added pin interrupt functionality for a push-button on INT0. Added Timer 0 functionality for timed polling of the push-button to detect a short / long press.
2018-10-16 Initial KiCAD Footprint Library
    KiCAD Footprint library added with modified MOSFET Driver Footprint
2018-10-18 GCEW Glove Schematic Update 3
    Finalized GCEW glove schematic. Added custom schematic symbols and footprints for glove components. Designed and Added PCB design files and Gerber Files for manufacturing.
2018-10-19 GCEW Glove Schematic Update 4
    Fixed PCB design error with Bluetooth module. Added additional labels on silkscreen layers.
2018-10-19 schematic is dramatic
    co
2018-10-19 kicad
    micromanage
2018-10-23 GCEW Glove Gerber Zip Fix
2018-10-23 Glove and Motor Controller Base Code
2018-10-23 First Upload
2018-10-23 Footprint Fix
2018-10-23 Summary2
2018-10-24 Removed Incorrect Gerber Stencil Zip
2018-10-24 GCEW Motor Controller Schematic Update 1
2018-10-24 GCEW Motor Controller Schematic Update 2
2018-10-24 GCEW Motor Controller Schematic Update 3
2018-10-24 GCEW Motor Controller Schematic Update 4
2018-10-25 GCEW Motor Controller Schematic Update 5
    Finalized KiCAD GCEW Motor Controller Schematic. Initial KiCAD Motor Controller PCB Design.
2018-10-25 KiCAD Motor Controller MCU Schematic Update 1
    Began KiCAD Schematic Design of Motor Controller MCU Board
2018-10-26 GCEW Motor Controller Schematic Update 5
2018-10-27 GCEW Motor Controller PCB Update 1
    17 Connections left to complete. Still need to finalize board outline dimensions.
2018-10-28 GCEW Motor Controller PCB Update 1
    Completed GCEW Motor Controller PCB Design.
2018-10-28 GCEW Motor Controller PCB Update 3
    Corrected front silkscreen error
2018-10-29 GCEW Motor Controller PCB Update 4
    Added BOM file for Motor Controller and Glove Board
2018-10-30 Intial Motor Controller MCU Schematic / PCB Upload
2018-10-30 Saved
2018-10-30 GCEW Motor Controller MCU PCB Update 1
    Finished PCB track layout. Need to finish adding text to bottom silkscreen layer.
2018-10-30 GCEW Motor Controller MCU PCB Update 2
    Finalized GCEW Motor Controller MCU PCB. Added bottom silkscreen text for input connectors. Generated gerber files for manufacturer.
2018-11-03 GCEW Kicad BOM Added
2018-11-05 ADC Commands
    Add command determination
2018-11-05 Add uart to motor controller project
2018-11-05 read in command, work on determining state
2018-11-05 Base current speed off of previous speed
2018-11-05 Smoother transitions
2018-11-05 todo add
2018-11-07 rev one at ramp speeds
2018-11-07 update ramping algorithm
2018-11-07 edit ramping
2018-11-07 change MOTOR_SPEEDS to 16 bit
2018-11-07 Use math to determine ramp rather than if statements
    if goal > current, goal-current will be positive and ramp up
    if goal < current, goal-current will be negative and ramp down
    if goal == current, goal-current will be zero
2018-11-07 update ramping, add change in directions
2018-11-07 define constant number of steps
2018-11-07 use pwm register values
2018-11-07 add todo
2018-11-07 add averaging
2018-11-07 exit modes on button press
2018-11-07 return to start after calibration
2018-11-08 fix errors
2018-11-08 test ISR
2018-11-08 working on interrupt
2018-11-08 with button - interrupt restarts main function
2018-11-08 ADC working and determining commands
2018-11-09 working for pins on pcb
2018-11-09 only print commands
2018-11-09 switch fore finger and ring finger
2018-11-09 set up pwm settings
2018-11-09 print and led for testing
2018-11-11 bluetooth working for connection but not sending correct data
2018-11-12 Working Glove Commands
2018-11-12 Glove PWM Working
2018-11-12 Fully Working Glove to MCU PWM
2018-12-12 Reorganized Files
2018-12-12 Reoragnized KiCAD
